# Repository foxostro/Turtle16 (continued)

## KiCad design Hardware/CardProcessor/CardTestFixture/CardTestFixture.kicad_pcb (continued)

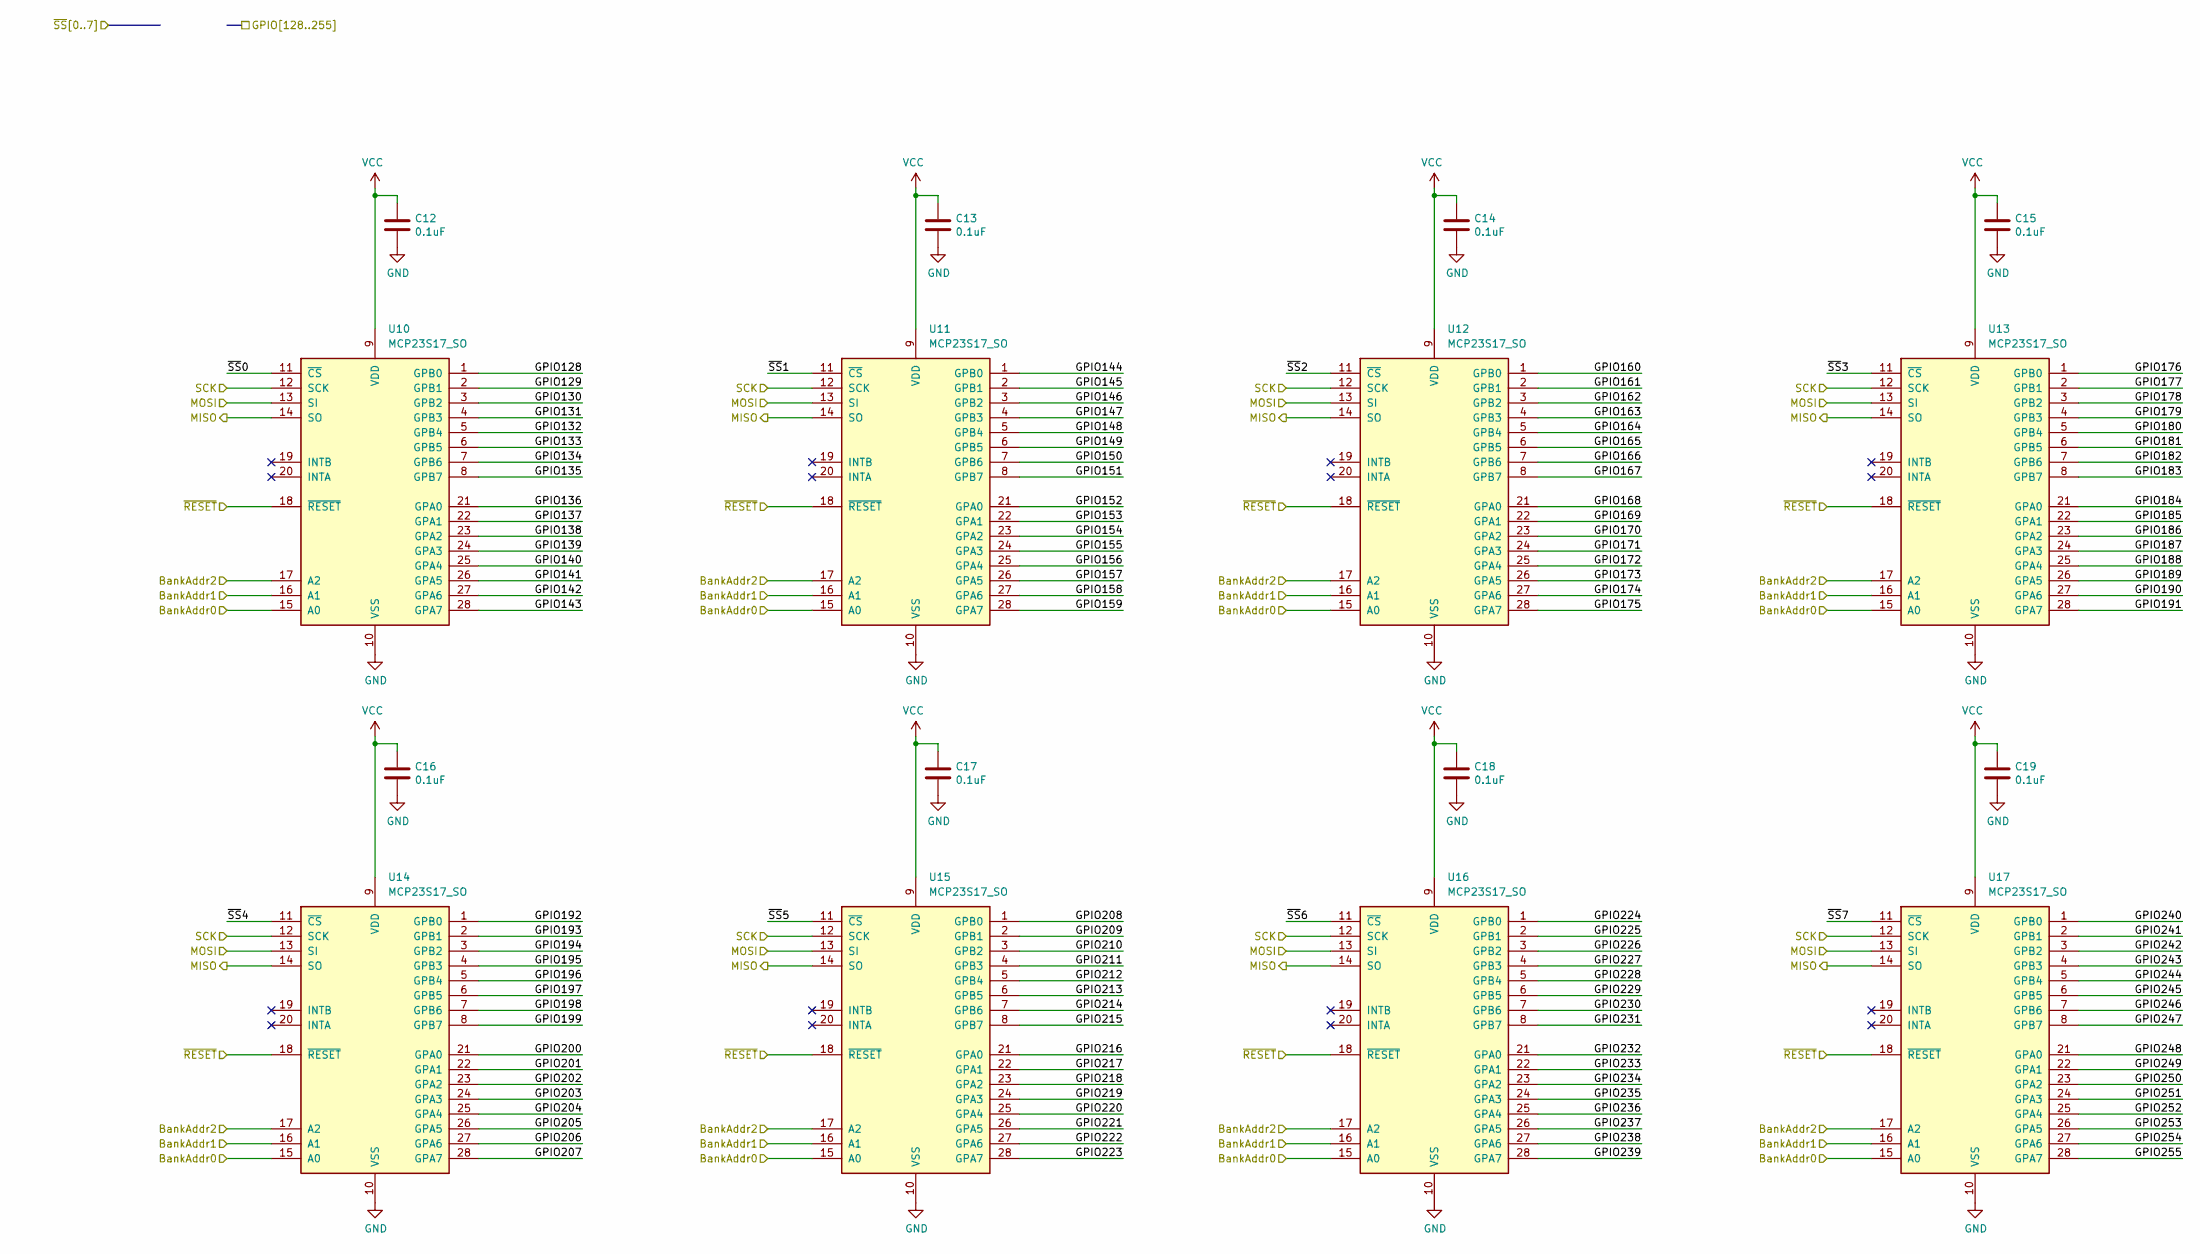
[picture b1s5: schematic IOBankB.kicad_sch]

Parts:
C12, C13, C14, C15, C16, C17, C18, C19: 0.1uF; C_0603_1608Metric; Manufacturer# EMK107B7104KAHT; Mouser# 963-EMK107B7104KAHT
U10, U11, U12, U13, U14, U15, U16, U17: MCP23S17_SO; SOIC-28W_7.5x17.9mm_P1.27mm

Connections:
/GPIO128: U10.1 (GPB0); also elsewhere on the board
/GPIO129: U10.2 (GPB1); also elsewhere on the board
/GPIO130: U10.3 (GPB2); also elsewhere on the board
/GPIO131: U10.4 (GPB3); also elsewhere on the board
/GPIO132: U10.5 (GPB4); also elsewhere on the board
/GPIO133: U10.6 (GPB5); also elsewhere on the board
/GPIO134: U10.7 (GPB6); also elsewhere on the board
/GPIO135: U10.8 (GPB7); also elsewhere on the board
/GPIO136: U10.21 (GPA0); also elsewhere on the board
/GPIO137: U10.22 (GPA1); also elsewhere on the board
/GPIO138: U10.23 (GPA2); also elsewhere on the board
/GPIO139: U10.24 (GPA3); also elsewhere on the board
/GPIO140: U10.25 (GPA4); also elsewhere on the board
/GPIO141: U10.26 (GPA5); also elsewhere on the board
/GPIO142: U10.27 (GPA6); also elsewhere on the board
/GPIO143: U10.28 (GPA7); also elsewhere on the board
/GPIO144: U11.1 (GPB0); also elsewhere on the board
/GPIO145: U11.2 (GPB1); also elsewhere on the board
/GPIO146: U11.3 (GPB2); also elsewhere on the board
/GPIO147: U11.4 (GPB3); also elsewhere on the board
/GPIO148: U11.5 (GPB4); also elsewhere on the board
/GPIO149: U11.6 (GPB5); also elsewhere on the board
/GPIO150: U11.7 (GPB6); also elsewhere on the board
/GPIO151: U11.8 (GPB7); also elsewhere on the board
/GPIO152: U11.21 (GPA0); also elsewhere on the board
/GPIO153: U11.22 (GPA1); also elsewhere on the board
/GPIO154: U11.23 (GPA2); also elsewhere on the board
/GPIO155: U11.24 (GPA3); also elsewhere on the board
/GPIO156: U11.25 (GPA4); also elsewhere on the board
/GPIO157: U11.26 (GPA5); also elsewhere on the board
/GPIO158: U11.27 (GPA6); also elsewhere on the board
/GPIO159: U11.28 (GPA7); also elsewhere on the board
/GPIO160: U12.1 (GPB0); also elsewhere on the board
/GPIO161: U12.2 (GPB1); also elsewhere on the board
/GPIO162: U12.3 (GPB2); also elsewhere on the board
/GPIO163: U12.4 (GPB3); also elsewhere on the board
/GPIO164: U12.5 (GPB4); also elsewhere on the board
/GPIO165: U12.6 (GPB5); also elsewhere on the board
/GPIO166: U12.7 (GPB6); also elsewhere on the board
/GPIO167: U12.8 (GPB7); also elsewhere on the board
/GPIO168: U12.21 (GPA0); also elsewhere on the board
/GPIO169: U12.22 (GPA1); also elsewhere on the board
/GPIO170: U12.23 (GPA2); also elsewhere on the board
/GPIO171: U12.24 (GPA3); also elsewhere on the board
/GPIO172: U12.25 (GPA4); also elsewhere on the board
/GPIO173: U12.26 (GPA5); also elsewhere on the board
/GPIO174: U12.27 (GPA6); also elsewhere on the board
/GPIO175: U12.28 (GPA7); also elsewhere on the board
/GPIO176: U13.1 (GPB0); also elsewhere on the board
/GPIO177: U13.2 (GPB1); also elsewhere on the board
/GPIO178: U13.3 (GPB2); also elsewhere on the board
/GPIO179: U13.4 (GPB3); also elsewhere on the board
/GPIO180: U13.5 (GPB4); also elsewhere on the board
/GPIO181: U13.6 (GPB5); also elsewhere on the board
/GPIO182: U13.7 (GPB6); also elsewhere on the board
/GPIO183: U13.8 (GPB7); also elsewhere on the board
/GPIO184: U13.21 (GPA0); also elsewhere on the board
/GPIO185: U13.22 (GPA1); also elsewhere on the board
/GPIO186: U13.23 (GPA2); also elsewhere on the board
/GPIO187: U13.24 (GPA3); also elsewhere on the board
/GPIO188: U13.25 (GPA4); also elsewhere on the board
/GPIO189: U13.26 (GPA5); also elsewhere on the board
/GPIO190: U13.27 (GPA6); also elsewhere on the board
/GPIO191: U13.28 (GPA7); also elsewhere on the board
/GPIO192: U14.1 (GPB0); also elsewhere on the board
/GPIO193: U14.2 (GPB1); also elsewhere on the board
/GPIO194: U14.3 (GPB2); also elsewhere on the board
/GPIO195: U14.4 (GPB3); also elsewhere on the board
/GPIO196: U14.5 (GPB4); also elsewhere on the board
/GPIO197: U14.6 (GPB5); also elsewhere on the board
/GPIO198: U14.7 (GPB6); also elsewhere on the board
/GPIO199: U14.8 (GPB7); also elsewhere on the board
/GPIO200: U14.21 (GPA0); also elsewhere on the board
/GPIO201: U14.22 (GPA1); also elsewhere on the board
/GPIO202: U14.23 (GPA2); also elsewhere on the board
/GPIO203: U14.24 (GPA3); also elsewhere on the board
/GPIO204: U14.25 (GPA4); also elsewhere on the board
/GPIO205: U14.26 (GPA5); also elsewhere on the board
/GPIO206: U14.27 (GPA6); also elsewhere on the board
/GPIO207: U14.28 (GPA7); also elsewhere on the board
/GPIO208: U15.1 (GPB0); also elsewhere on the board
/GPIO209: U15.2 (GPB1); also elsewhere on the board
/GPIO210: U15.3 (GPB2); also elsewhere on the board
/GPIO211: U15.4 (GPB3); also elsewhere on the board
/GPIO212: U15.5 (GPB4); also elsewhere on the board
/GPIO213: U15.6 (GPB5); also elsewhere on the board
/GPIO214: U15.7 (GPB6); also elsewhere on the board
/GPIO215: U15.8 (GPB7); also elsewhere on the board
/GPIO216: U15.21 (GPA0); also elsewhere on the board
/GPIO217: U15.22 (GPA1); also elsewhere on the board
/GPIO218: U15.23 (GPA2); also elsewhere on the board
/GPIO219: U15.24 (GPA3); also elsewhere on the board
/GPIO220: U15.25 (GPA4); also elsewhere on the board
/GPIO221: U15.26 (GPA5); also elsewhere on the board
/GPIO222: U15.27 (GPA6); also elsewhere on the board
/GPIO223: U15.28 (GPA7); also elsewhere on the board
/GPIO224: U16.1 (GPB0); also elsewhere on the board
/GPIO225: U16.2 (GPB1); also elsewhere on the board
/GPIO226: U16.3 (GPB2); also elsewhere on the board
/GPIO227: U16.4 (GPB3); also elsewhere on the board
/GPIO228: U16.5 (GPB4); also elsewhere on the board
/GPIO229: U16.6 (GPB5); also elsewhere on the board
/GPIO230: U16.7 (GPB6); also elsewhere on the board
/GPIO231: U16.8 (GPB7); also elsewhere on the board
/GPIO232: U16.21 (GPA0); also elsewhere on the board
/GPIO233: U16.22 (GPA1); also elsewhere on the board
/GPIO234: U16.23 (GPA2); also elsewhere on the board
/GPIO235: U16.24 (GPA3); also elsewhere on the board
/GPIO236: U16.25 (GPA4); also elsewhere on the board
/GPIO237: U16.26 (GPA5); also elsewhere on the board
/GPIO238: U16.27 (GPA6); also elsewhere on the board
/GPIO239: U16.28 (GPA7); also elsewhere on the board
/GPIO240: U17.1 (GPB0); also elsewhere on the board
/GPIO241: U17.2 (GPB1); also elsewhere on the board
/GPIO242: U17.3 (GPB2); also elsewhere on the board
/GPIO243: U17.4 (GPB3); also elsewhere on the board
/GPIO244: U17.5 (GPB4); also elsewhere on the board
/GPIO245: U17.6 (GPB5); also elsewhere on the board
/GPIO246: U17.7 (GPB6); also elsewhere on the board
/GPIO247: U17.8 (GPB7); also elsewhere on the board
/GPIO248: U17.21 (GPA0); also elsewhere on the board
/GPIO249: U17.22 (GPA1); also elsewhere on the board
/GPIO250: U17.23 (GPA2); also elsewhere on the board
/GPIO251: U17.24 (GPA3); also elsewhere on the board
/GPIO252: U17.25 (GPA4); also elsewhere on the board
/GPIO253: U17.26 (GPA5); also elsewhere on the board
/GPIO254: U17.27 (GPA6); also elsewhere on the board
/GPIO255: U17.28 (GPA7); also elsewhere on the board
/MISO: U10.14 (SO), U11.14 (SO), U12.14 (SO), U13.14 (SO), U14.14 (SO), U15.14 (SO), U16.14 (SO), U17.14 (SO); also elsewhere on the board
/MOSI: U10.13 (SI), U11.13 (SI), U12.13 (SI), U13.13 (SI), U14.13 (SI), U15.13 (SI), U16.13 (SI), U17.13 (SI); also elsewhere on the board
/SCK: U10.12 (SCK), U11.12 (SCK), U12.12 (SCK), U13.12 (SCK), U14.12 (SCK), U15.12 (SCK), U16.12 (SCK), U17.12 (SCK); also elsewhere on the board
/~RESET: U10.18 (~RESET), U11.18 (~RESET), U12.18 (~RESET), U13.18 (~RESET), U14.18 (~RESET), U15.18 (~RESET), U16.18 (~RESET), U17.18 (~RESET); also elsewhere on the board
/~SS0: U10.11 (~CS); also elsewhere on the board
/~SS1: U11.11 (~CS); also elsewhere on the board
/~SS2: U12.11 (~CS); also elsewhere on the board
/~SS3: U13.11 (~CS); also elsewhere on the board
/~SS4: U14.11 (~CS); also elsewhere on the board
/~SS5: U15.11 (~CS); also elsewhere on the board
/~SS6: U16.11 (~CS); also elsewhere on the board
/~SS7: U17.11 (~CS); also elsewhere on the board
GND: C12.2, C13.2, C14.2, C15.2, C16.2, C17.2, C18.2, C19.2, U10.10 (VSS), U10.16 (A1), U10.17 (A2), U11.10 (VSS), U11.16 (A1), U11.17 (A2), U12.10 (VSS), U12.16 (A1), U12.17 (A2), U13.10 (VSS), U13.16 (A1), U13.17 (A2), U14.10 (VSS), U14.16 (A1), U14.17 (A2), U15.10 (VSS), U15.16 (A1), U15.17 (A2), U16.10 (VSS), U16.16 (A1), U16.17 (A2), U17.10 (VSS), U17.16 (A1), U17.17 (A2); also elsewhere on the board
VCC: C12.1, C13.1, C14.1, C15.1, C16.1, C17.1, C18.1, C19.1, U10.9 (VDD), U10.15 (A0), U11.9 (VDD), U11.15 (A0), U12.9 (VDD), U12.15 (A0), U13.9 (VDD), U13.15 (A0), U14.9 (VDD), U14.15 (A0), U15.9 (VDD), U15.15 (A0), U16.9 (VDD), U16.15 (A0), U17.9 (VDD), U17.15 (A0); also elsewhere on the board

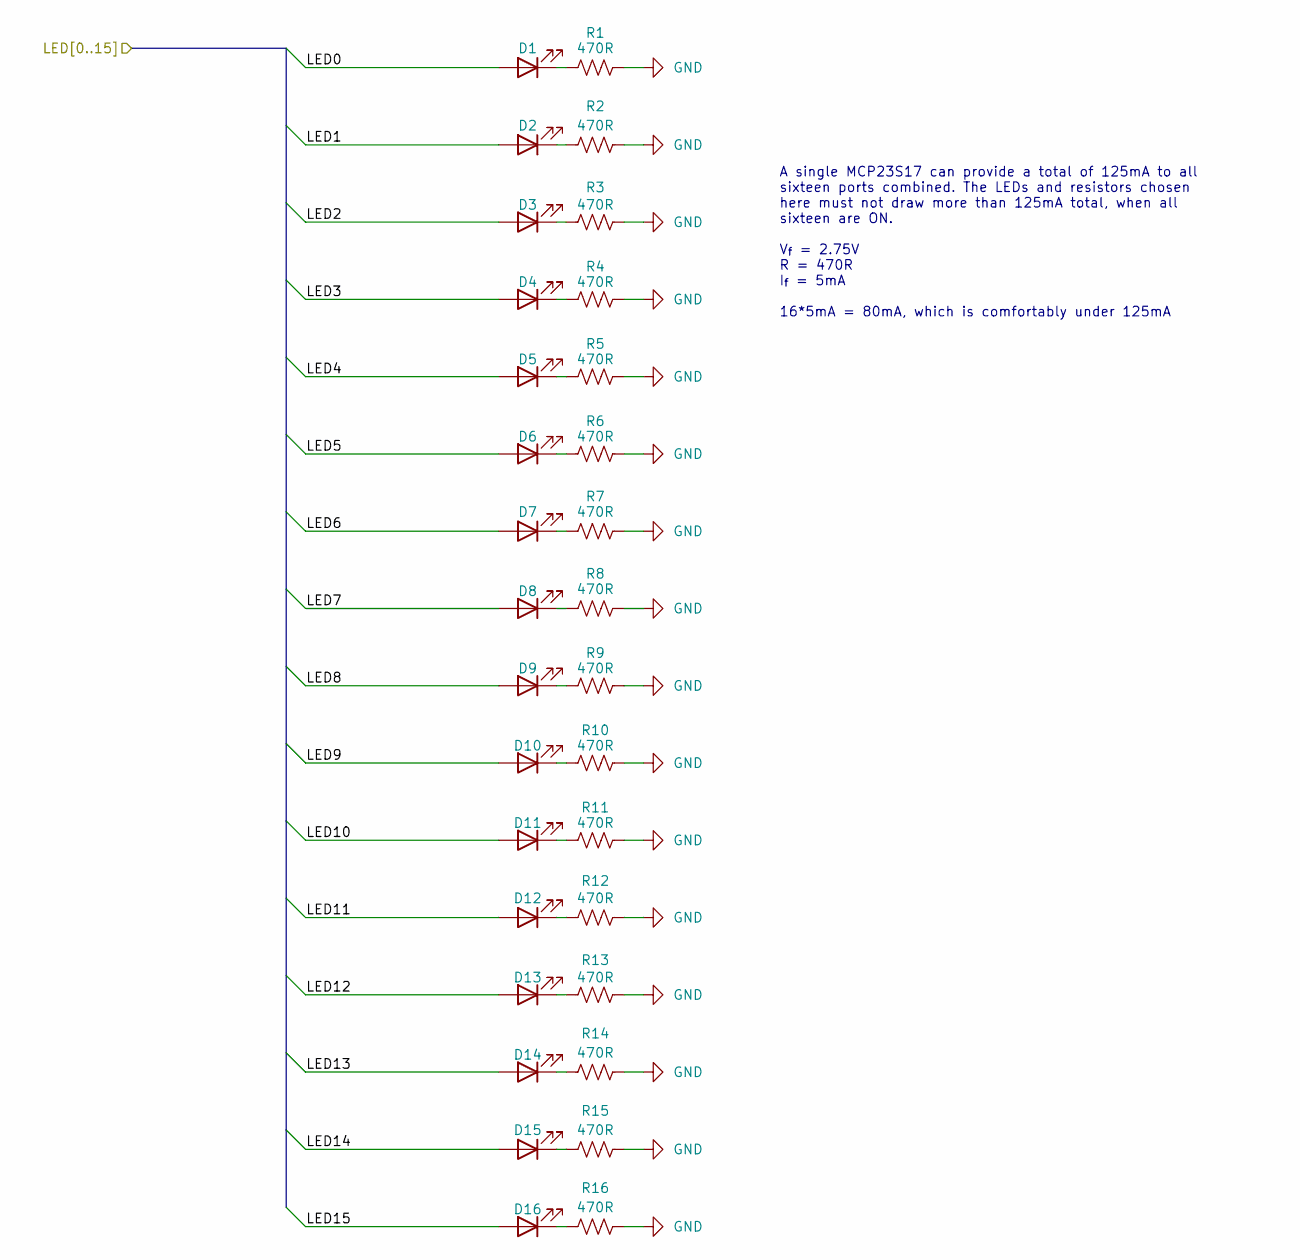
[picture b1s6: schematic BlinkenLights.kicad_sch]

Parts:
D1, D2, D3, D4, D5, D6, D7, D8, D9, D10, D11, D12, D13, D14, D15, D16: LED_0603_1608Metric
R1, R2, R3, R4, R5, R6, R7, R8, R9, R10, R11, R12, R13, R14, R15, R16: 470R; C_0603_1608Metric

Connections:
/GPIO280: D1.2 (A); also elsewhere on the board
/GPIO281: D2.2 (A); also elsewhere on the board
/GPIO282: D3.2 (A); also elsewhere on the board
/GPIO283: D4.2 (A); also elsewhere on the board
/GPIO284: D5.2 (A); also elsewhere on the board
/GPIO285: D6.2 (A); also elsewhere on the board
/GPIO286: D7.2 (A); also elsewhere on the board
/GPIO287: D8.2 (A); also elsewhere on the board
/GPIO288: D9.2 (A); also elsewhere on the board
/GPIO289: D10.2 (A); also elsewhere on the board
/GPIO290: D11.2 (A); also elsewhere on the board
/GPIO291: D12.2 (A); also elsewhere on the board
/GPIO292: D13.2 (A); also elsewhere on the board
/GPIO293: D14.2 (A); also elsewhere on the board
/GPIO294: D15.2 (A); also elsewhere on the board
/GPIO295: D16.2 (A); also elsewhere on the board
GND: R1.2, R2.2, R3.2, R4.2, R5.2, R6.2, R7.2, R8.2, R9.2, R10.2, R11.2, R12.2, R13.2, R14.2, R15.2, R16.2; also elsewhere on the board
unnamed: D1.1 (K), R1.1
unnamed: D2.1 (K), R2.1
unnamed: D3.1 (K), R3.1
unnamed: D4.1 (K), R4.1
unnamed: D5.1 (K), R5.1
unnamed: D6.1 (K), R6.1
unnamed: D7.1 (K), R7.1
unnamed: D8.1 (K), R8.1
unnamed: D9.1 (K), R9.1
unnamed: D10.1 (K), R10.1
unnamed: D11.1 (K), R11.1
unnamed: D12.1 (K), R12.1
unnamed: D13.1 (K), R13.1
unnamed: D14.1 (K), R14.1
unnamed: D15.1 (K), R15.1
unnamed: D16.1 (K), R16.1

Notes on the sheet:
A single MCP23S17 can provide a total of 125mA to all sixteen ports combined. The LEDs and resistors chosen here must not draw more than 125mA total, when all sixteen are ON. V_{f} = 2.75V R = 470R I_{f} = 5mA 16*5mA = 80mA, which is comfortably under 125mA

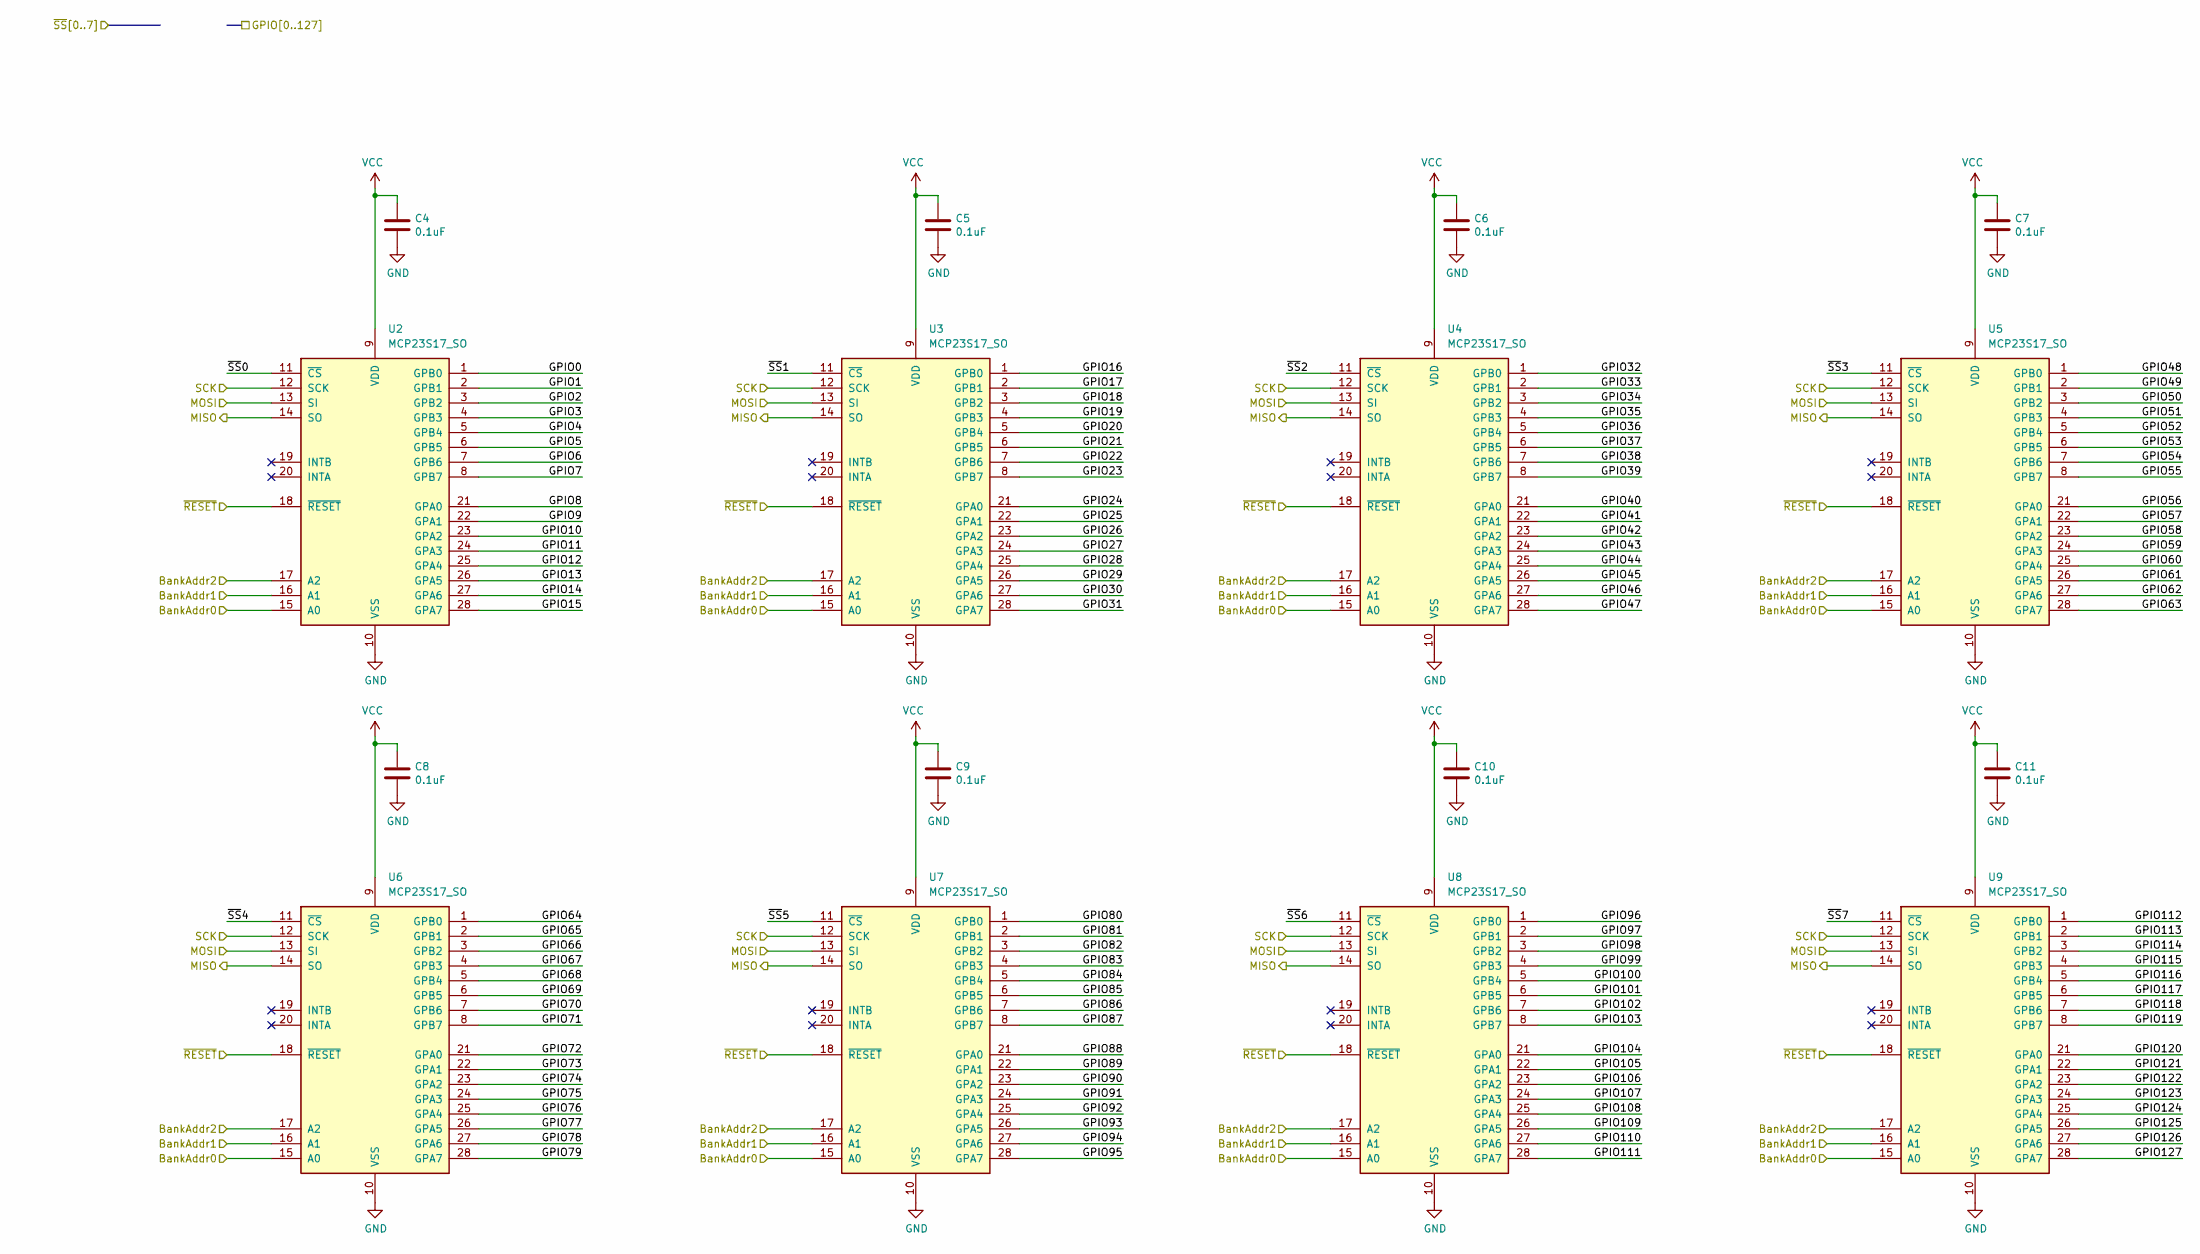
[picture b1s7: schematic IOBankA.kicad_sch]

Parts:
C4, C5, C6, C7, C8, C9, C10, C11: 0.1uF; C_0603_1608Metric; Manufacturer# EMK107B7104KAHT; Mouser# 963-EMK107B7104KAHT
U2, U3, U4, U5, U6, U7, U8, U9: MCP23S17_SO; SOIC-28W_7.5x17.9mm_P1.27mm

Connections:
/GPIO0: U2.1 (GPB0); also elsewhere on the board
/GPIO1: U2.2 (GPB1); also elsewhere on the board
/GPIO2: U2.3 (GPB2); also elsewhere on the board
/GPIO3: U2.4 (GPB3); also elsewhere on the board
/GPIO4: U2.5 (GPB4)
/GPIO5: U2.6 (GPB5)
/GPIO6: U2.7 (GPB6)
/GPIO7: U2.8 (GPB7)
/GPIO8: U2.21 (GPA0)
/GPIO9: U2.22 (GPA1)
/GPIO10: U2.23 (GPA2)
/GPIO11: U2.24 (GPA3); also elsewhere on the board
/GPIO12: U2.25 (GPA4); also elsewhere on the board
/GPIO13: U2.26 (GPA5); also elsewhere on the board
/GPIO14: U2.27 (GPA6); also elsewhere on the board
/GPIO15: U2.28 (GPA7); also elsewhere on the board
/GPIO16: U3.1 (GPB0); also elsewhere on the board
/GPIO17: U3.2 (GPB1); also elsewhere on the board
/GPIO18: U3.3 (GPB2); also elsewhere on the board
/GPIO19: U3.4 (GPB3); also elsewhere on the board
/GPIO20: U3.5 (GPB4); also elsewhere on the board
/GPIO21: U3.6 (GPB5); also elsewhere on the board
/GPIO22: U3.7 (GPB6); also elsewhere on the board
/GPIO23: U3.8 (GPB7); also elsewhere on the board
/GPIO24: U3.21 (GPA0); also elsewhere on the board
/GPIO25: U3.22 (GPA1); also elsewhere on the board
/GPIO26: U3.23 (GPA2); also elsewhere on the board
/GPIO27: U3.24 (GPA3); also elsewhere on the board
/GPIO28: U3.25 (GPA4); also elsewhere on the board
/GPIO29: U3.26 (GPA5); also elsewhere on the board
/GPIO30: U3.27 (GPA6); also elsewhere on the board
/GPIO31: U3.28 (GPA7); also elsewhere on the board
/GPIO32: U4.1 (GPB0); also elsewhere on the board
/GPIO33: U4.2 (GPB1); also elsewhere on the board
/GPIO34: U4.3 (GPB2); also elsewhere on the board
/GPIO35: U4.4 (GPB3); also elsewhere on the board
/GPIO36: U4.5 (GPB4); also elsewhere on the board
/GPIO37: U4.6 (GPB5); also elsewhere on the board
/GPIO38: U4.7 (GPB6); also elsewhere on the board
/GPIO39: U4.8 (GPB7); also elsewhere on the board
/GPIO40: U4.21 (GPA0); also elsewhere on the board
/GPIO41: U4.22 (GPA1); also elsewhere on the board
/GPIO42: U4.23 (GPA2); also elsewhere on the board
/GPIO43: U4.24 (GPA3); also elsewhere on the board
/GPIO44: U4.25 (GPA4); also elsewhere on the board
/GPIO45: U4.26 (GPA5); also elsewhere on the board
/GPIO46: U4.27 (GPA6); also elsewhere on the board
/GPIO47: U4.28 (GPA7); also elsewhere on the board
/GPIO48: U5.1 (GPB0); also elsewhere on the board
/GPIO49: U5.2 (GPB1); also elsewhere on the board
/GPIO50: U5.3 (GPB2); also elsewhere on the board
/GPIO51: U5.4 (GPB3); also elsewhere on the board
/GPIO52: U5.5 (GPB4); also elsewhere on the board
/GPIO53: U5.6 (GPB5); also elsewhere on the board
/GPIO54: U5.7 (GPB6); also elsewhere on the board
/GPIO55: U5.8 (GPB7); also elsewhere on the board
/GPIO56: U5.21 (GPA0); also elsewhere on the board
/GPIO57: U5.22 (GPA1); also elsewhere on the board
/GPIO58: U5.23 (GPA2); also elsewhere on the board
/GPIO59: U5.24 (GPA3); also elsewhere on the board
/GPIO60: U5.25 (GPA4); also elsewhere on the board
/GPIO61: U5.26 (GPA5); also elsewhere on the board
/GPIO62: U5.27 (GPA6); also elsewhere on the board
/GPIO63: U5.28 (GPA7); also elsewhere on the board
/GPIO64: U6.1 (GPB0); also elsewhere on the board
/GPIO65: U6.2 (GPB1); also elsewhere on the board
/GPIO66: U6.3 (GPB2); also elsewhere on the board
/GPIO67: U6.4 (GPB3); also elsewhere on the board
/GPIO68: U6.5 (GPB4); also elsewhere on the board
/GPIO69: U6.6 (GPB5); also elsewhere on the board
/GPIO70: U6.7 (GPB6); also elsewhere on the board
/GPIO71: U6.8 (GPB7); also elsewhere on the board
/GPIO72: U6.21 (GPA0); also elsewhere on the board
/GPIO73: U6.22 (GPA1); also elsewhere on the board
/GPIO74: U6.23 (GPA2); also elsewhere on the board
/GPIO75: U6.24 (GPA3); also elsewhere on the board
/GPIO76: U6.25 (GPA4); also elsewhere on the board
/GPIO77: U6.26 (GPA5); also elsewhere on the board
/GPIO78: U6.27 (GPA6); also elsewhere on the board
/GPIO79: U6.28 (GPA7); also elsewhere on the board
/GPIO80: U7.1 (GPB0); also elsewhere on the board
/GPIO81: U7.2 (GPB1); also elsewhere on the board
/GPIO82: U7.3 (GPB2); also elsewhere on the board
/GPIO83: U7.4 (GPB3); also elsewhere on the board
/GPIO84: U7.5 (GPB4); also elsewhere on the board
/GPIO85: U7.6 (GPB5); also elsewhere on the board
/GPIO86: U7.7 (GPB6); also elsewhere on the board
/GPIO87: U7.8 (GPB7); also elsewhere on the board
/GPIO88: U7.21 (GPA0); also elsewhere on the board
/GPIO89: U7.22 (GPA1); also elsewhere on the board
/GPIO90: U7.23 (GPA2); also elsewhere on the board
/GPIO91: U7.24 (GPA3); also elsewhere on the board
/GPIO92: U7.25 (GPA4); also elsewhere on the board
/GPIO93: U7.26 (GPA5); also elsewhere on the board
/GPIO94: U7.27 (GPA6); also elsewhere on the board
/GPIO95: U7.28 (GPA7); also elsewhere on the board
/GPIO96: U8.1 (GPB0); also elsewhere on the board
/GPIO97: U8.2 (GPB1); also elsewhere on the board
/GPIO98: U8.3 (GPB2); also elsewhere on the board
/GPIO99: U8.4 (GPB3); also elsewhere on the board
/GPIO100: U8.5 (GPB4); also elsewhere on the board
/GPIO101: U8.6 (GPB5); also elsewhere on the board
/GPIO102: U8.7 (GPB6); also elsewhere on the board
/GPIO103: U8.8 (GPB7); also elsewhere on the board
/GPIO104: U8.21 (GPA0); also elsewhere on the board
/GPIO105: U8.22 (GPA1); also elsewhere on the board
/GPIO106: U8.23 (GPA2); also elsewhere on the board
/GPIO107: U8.24 (GPA3); also elsewhere on the board
/GPIO108: U8.25 (GPA4); also elsewhere on the board
/GPIO109: U8.26 (GPA5); also elsewhere on the board
/GPIO110: U8.27 (GPA6); also elsewhere on the board
/GPIO111: U8.28 (GPA7); also elsewhere on the board
/GPIO112: U9.1 (GPB0); also elsewhere on the board
/GPIO113: U9.2 (GPB1); also elsewhere on the board
/GPIO114: U9.3 (GPB2); also elsewhere on the board
/GPIO115: U9.4 (GPB3); also elsewhere on the board
/GPIO116: U9.5 (GPB4); also elsewhere on the board
/GPIO117: U9.6 (GPB5); also elsewhere on the board
/GPIO118: U9.7 (GPB6); also elsewhere on the board
/GPIO119: U9.8 (GPB7); also elsewhere on the board
/GPIO120: U9.21 (GPA0); also elsewhere on the board
/GPIO121: U9.22 (GPA1); also elsewhere on the board
/GPIO122: U9.23 (GPA2); also elsewhere on the board
/GPIO123: U9.24 (GPA3); also elsewhere on the board
/GPIO124: U9.25 (GPA4); also elsewhere on the board
/GPIO125: U9.26 (GPA5); also elsewhere on the board
/GPIO126: U9.27 (GPA6); also elsewhere on the board
/GPIO127: U9.28 (GPA7); also elsewhere on the board
/MISO: U2.14 (SO), U3.14 (SO), U4.14 (SO), U5.14 (SO), U6.14 (SO), U7.14 (SO), U8.14 (SO), U9.14 (SO); also elsewhere on the board
/MOSI: U2.13 (SI), U3.13 (SI), U4.13 (SI), U5.13 (SI), U6.13 (SI), U7.13 (SI), U8.13 (SI), U9.13 (SI); also elsewhere on the board
/SCK: U2.12 (SCK), U3.12 (SCK), U4.12 (SCK), U5.12 (SCK), U6.12 (SCK), U7.12 (SCK), U8.12 (SCK), U9.12 (SCK); also elsewhere on the board
/~RESET: U2.18 (~RESET), U3.18 (~RESET), U4.18 (~RESET), U5.18 (~RESET), U6.18 (~RESET), U7.18 (~RESET), U8.18 (~RESET), U9.18 (~RESET); also elsewhere on the board
/~SS0: U2.11 (~CS); also elsewhere on the board
/~SS1: U3.11 (~CS); also elsewhere on the board
/~SS2: U4.11 (~CS); also elsewhere on the board
/~SS3: U5.11 (~CS); also elsewhere on the board
/~SS4: U6.11 (~CS); also elsewhere on the board
/~SS5: U7.11 (~CS); also elsewhere on the board
/~SS6: U8.11 (~CS); also elsewhere on the board
/~SS7: U9.11 (~CS); also elsewhere on the board
GND: C4.2, C5.2, C6.2, C7.2, C8.2, C9.2, C10.2, C11.2, U2.10 (VSS), U2.15 (A0), U2.16 (A1), U2.17 (A2), U3.10 (VSS), U3.15 (A0), U3.16 (A1), U3.17 (A2), U4.10 (VSS), U4.15 (A0), U4.16 (A1), U4.17 (A2), U5.10 (VSS), U5.15 (A0), U5.16 (A1), U5.17 (A2), U6.10 (VSS), U6.15 (A0), U6.16 (A1), U6.17 (A2), U7.10 (VSS), U7.15 (A0), U7.16 (A1), U7.17 (A2), U8.10 (VSS), U8.15 (A0), U8.16 (A1), U8.17 (A2), U9.10 (VSS), U9.15 (A0), U9.16 (A1), U9.17 (A2); also elsewhere on the board
VCC: C4.1, C5.1, C6.1, C7.1, C8.1, C9.1, C10.1, C11.1, U2.9 (VDD), U3.9 (VDD), U4.9 (VDD), U5.9 (VDD), U6.9 (VDD), U7.9 (VDD), U8.9 (VDD), U9.9 (VDD); also elsewhere on the board

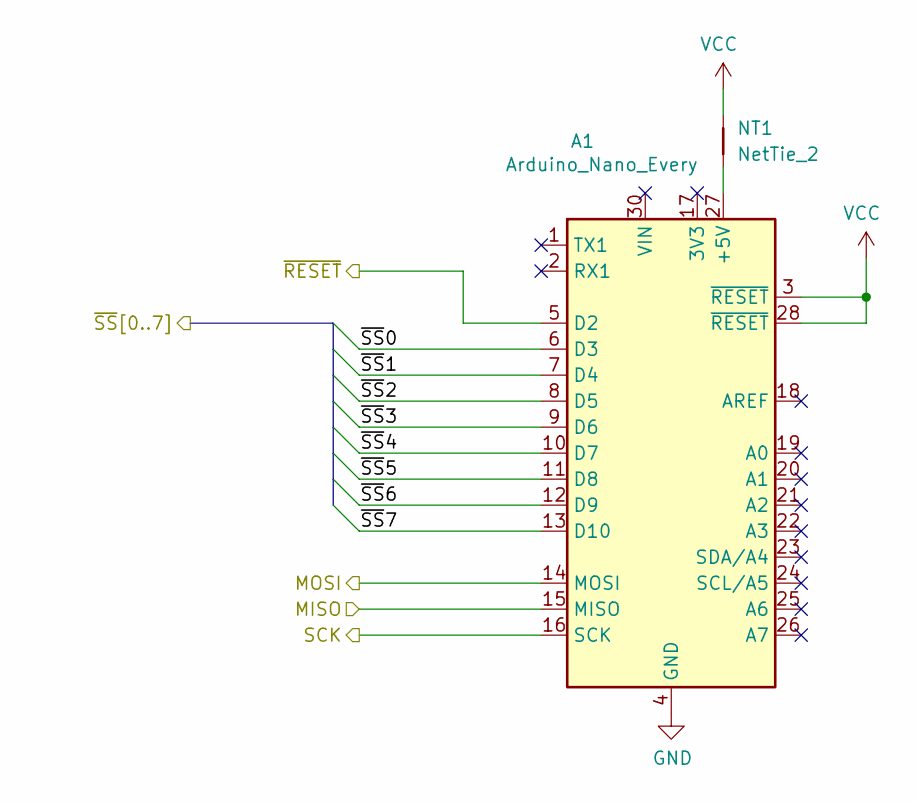
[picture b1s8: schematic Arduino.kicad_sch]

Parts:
A1: Arduino_Nano_Every; Arduino_Nano_Every_Castellated_Host
NT1: NetTie_2; NetTie-2_SMD_Pad0.5mm

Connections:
/MISO: A1.15 (MISO); also elsewhere on the board
/MOSI: A1.14 (MOSI); also elsewhere on the board
/SCK: A1.16 (SCK); also elsewhere on the board
/~RESET: A1.5 (D2); also elsewhere on the board
/~SS0: A1.6 (D3); also elsewhere on the board
/~SS1: A1.7 (D4); also elsewhere on the board
/~SS2: A1.8 (D5); also elsewhere on the board
/~SS3: A1.9 (D6); also elsewhere on the board
/~SS4: A1.10 (D7); also elsewhere on the board
/~SS5: A1.11 (D8); also elsewhere on the board
/~SS6: A1.12 (D9); also elsewhere on the board
/~SS7: A1.13 (D10); also elsewhere on the board
GND: A1.4 (GND), A1.29 (GND); also elsewhere on the board
unnamed: A1.27 (+5V), NT1.1
VCC: A1.3 (~RESET), A1.28 (~RESET), NT1.2; also elsewhere on the board

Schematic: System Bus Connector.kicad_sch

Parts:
J10: 71922-164LF; IDC-Header_2x32_P2.54mm_Horizontal; Manufacturer# 71922-164LF; Mouser# 649-71922-164LF

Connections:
/GPIO11: J10.59; also elsewhere on the board
/GPIO328: J10.7; also elsewhere on the board
/GPIO329: J10.8; also elsewhere on the board
/GPIO330: J10.9; also elsewhere on the board
/GPIO331: J10.10; also elsewhere on the board
/GPIO332: J10.13; also elsewhere on the board
/GPIO333: J10.14; also elsewhere on the board
/GPIO334: J10.15; also elsewhere on the board
/GPIO335: J10.16; also elsewhere on the board
/GPIO336: J10.19; also elsewhere on the board
/GPIO337: J10.20; also elsewhere on the board
/GPIO338: J10.21; also elsewhere on the board
/GPIO339: J10.22; also elsewhere on the board
/GPIO340: J10.25; also elsewhere on the board
/GPIO341: J10.26; also elsewhere on the board
/GPIO342: J10.27; also elsewhere on the board
/GPIO343: J10.28; also elsewhere on the board
/GPIO344: J10.51; also elsewhere on the board
/GPIO345: J10.52; also elsewhere on the board
/GPIO346: J10.49; also elsewhere on the board
/GPIO347: J10.50; also elsewhere on the board
/GPIO348: J10.45; also elsewhere on the board
/GPIO349: J10.46; also elsewhere on the board
/GPIO350: J10.43; also elsewhere on the board
/GPIO351: J10.44; also elsewhere on the board
/GPIO352: J10.39; also elsewhere on the board
/GPIO353: J10.40; also elsewhere on the board
/GPIO354: J10.37; also elsewhere on the board
/GPIO355: J10.38; also elsewhere on the board
/GPIO356: J10.33; also elsewhere on the board
/GPIO357: J10.34; also elsewhere on the board
/GPIO358: J10.31; also elsewhere on the board
/GPIO359: J10.32; also elsewhere on the board
/GPIO360: J10.1; also elsewhere on the board
/GPIO361: J10.2; also elsewhere on the board
/GPIO362: J10.3; also elsewhere on the board
/GPIO363: J10.56; also elsewhere on the board
/GPIO364: J10.55; also elsewhere on the board
/GPIO365: J10.60; also elsewhere on the board
/GPIO366: J10.62; also elsewhere on the board
/GPIO367: J10.61; also elsewhere on the board
GND: J10.5, J10.6, J10.11, J10.12, J10.17, J10.18, J10.23, J10.24, J10.29, J10.30, J10.35, J10.36, J10.41, J10.42, J10.47, J10.48, J10.53, J10.54; also elsewhere on the board
VCC: J10.57, J10.58, J10.63, J10.64; also elsewhere on the board

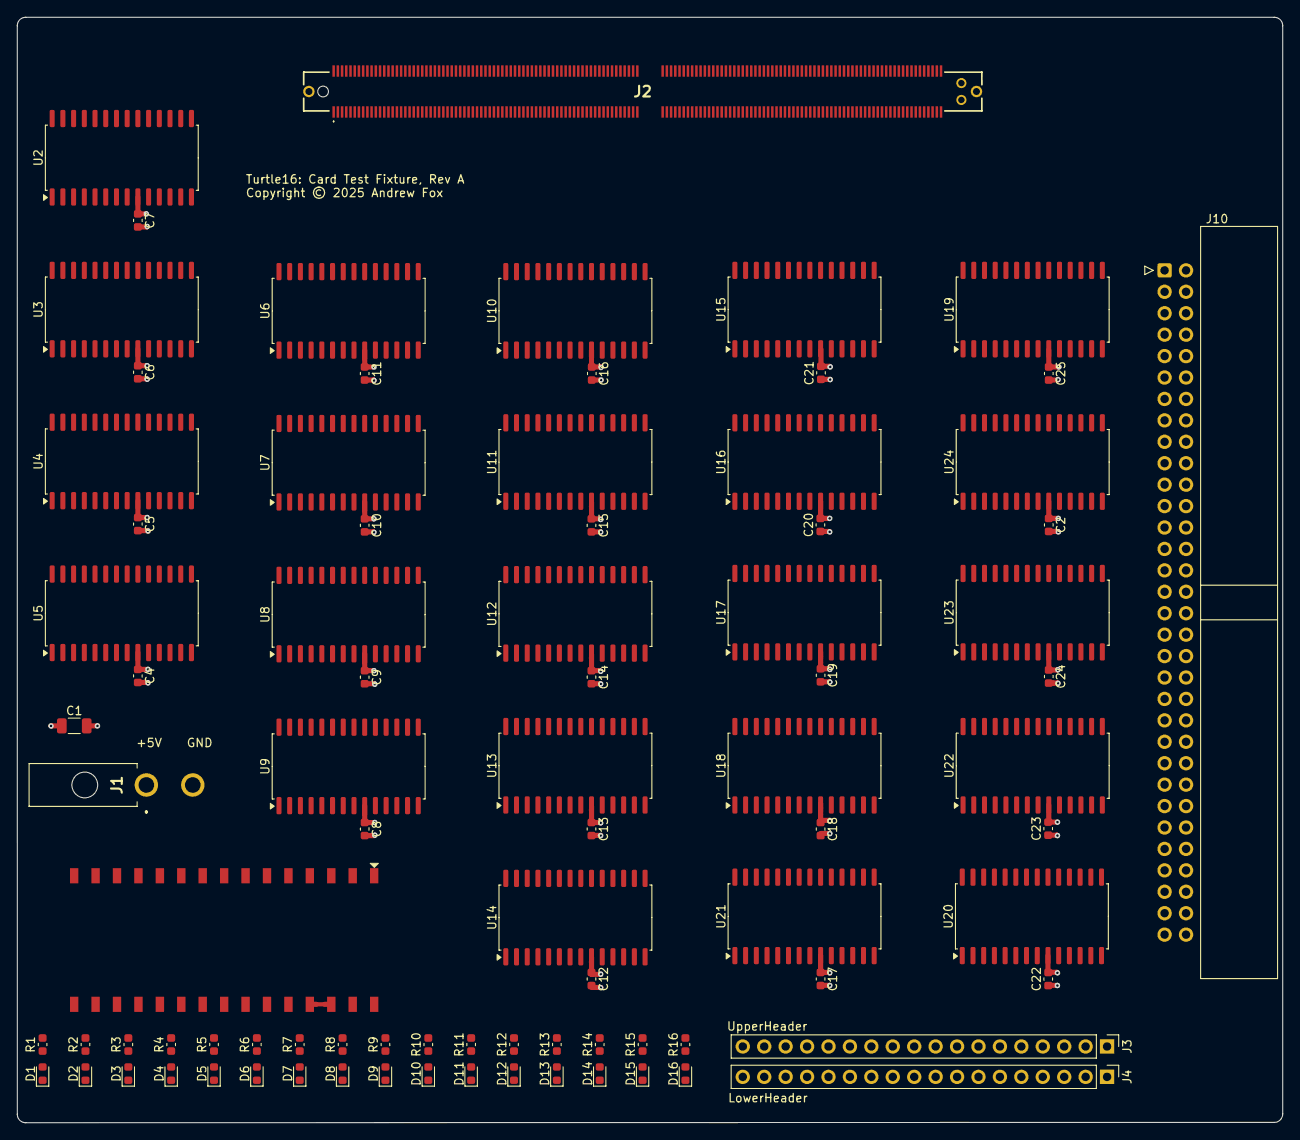
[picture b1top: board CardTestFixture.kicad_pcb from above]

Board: 8 copper layers, 150.0 x 131.0 mm, 86 parts (0 on the bottom side), 392 nets.
